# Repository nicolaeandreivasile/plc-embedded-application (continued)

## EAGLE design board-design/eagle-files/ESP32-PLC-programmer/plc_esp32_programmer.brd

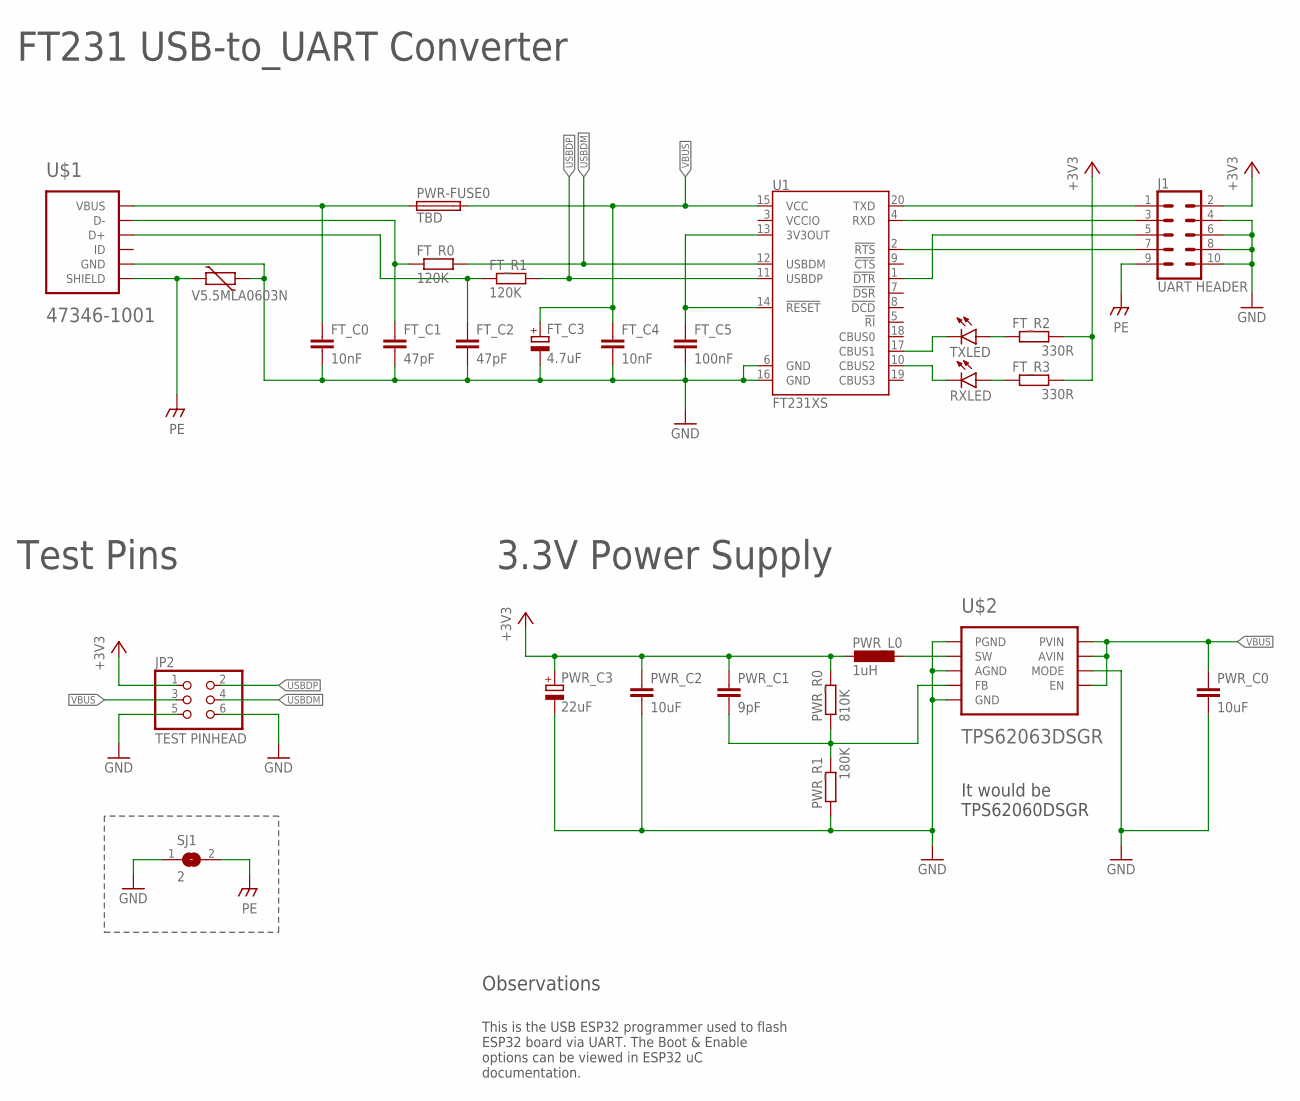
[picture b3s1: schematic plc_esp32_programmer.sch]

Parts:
FT_C0, FT_C4: 10nF; C0402
FT_C1, FT_C2: 47pF; C0402
FT_C3: 4.7uF; SMC_B
FT_C5: 100nF; C0402
FT_R0, FT_R1: 120K; R0402
FT_R2, FT_R3: 330R; R0402
J1: UART HEADER; 2X5-SHROUDED_SMD
JP2: TEST PINHEAD; 2X03
MCU_VAR1: V5.5MLA0603N; CT/CN0603
PWR-FUSE0: TBD; MF-SMDF050
PWR_C0, PWR_C2: 10uF; C0603
PWR_C1: 9pF; C0402
PWR_C3: 22uF; SMC_B
PWR_L0: 1uH; L1210
PWR_R0: 810K; R0402
PWR_R1: 180K; R0402
RXLED: LG_T679-E1F1-1; PLCC2
SJ1: 2; SJ
TXLED: LG_T679-E1F1-1; PLCC2
U1: FT231XS; SSOP20_L
U$1: 47346-1001
U$2: TPS62063DSGR; WSON-8

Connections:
+3V3: FT_R2.2, FT_R3.2, J1.2, JP2.1, PWR_C1.1, PWR_C2.1, PWR_C3.+, PWR_L0.2, PWR_R0.2
GND: FT_C0.2, FT_C1.2, FT_C2.2, FT_C3.-, FT_C4.2, FT_C5.2, J1.4, J1.6, J1.8, J1.10, JP2.5, JP2.6, MCU_VAR1.1, PWR_C0.2, PWR_C2.2, PWR_C3.-, PWR_R1.1, SJ1.1, U1.6 (GND), U1.16 (GND), U$1.5 (GND), U$2.1 (PGND), U$2.3 (AGND), U$2.6 (MODE), U$2.9 (GND), U$2.10 (GND), U$2.11 (GND)
unnamed: J1.1, U1.20 (TXD)
unnamed: J1.3, U1.4 (RXD)
unnamed: J1.7, U1.2 (!RTS)
unnamed: J1.5, U1.1 (!DTR)
unnamed: FT_C5.1, U1.13 (3V3OUT), U1.14 (!RESET)
unnamed: FT_C2.1, FT_R1.1, U$1.3 (D+)
unnamed: FT_C1.1, FT_R0.1, U$1.2 (D-)
unnamed: FT_C0.1, PWR-FUSE0.1, U$1.1 (VBUS)
unnamed: FT_R3.1, RXLED.A
unnamed: RXLED.C, U1.10 (CBUS2)
unnamed: PWR_L0.1, U$2.2 (SW)
unnamed: PWR_C1.2, PWR_R0.1, PWR_R1.2, U$2.4 (FB)
unnamed: FT_R2.1, TXLED.A
unnamed: TXLED.C, U1.17 (CBUS1)
PE: J1.9, MCU_VAR1.2, SJ1.2, U$1.6 (SHIELD), U$1.7 (SHIELD), U$1.8 (SHIELD), U$1.9 (SHIELD), U$1.10 (SHIELD), U$1.11 (SHIELD)
USBDM: FT_R0.2, JP2.4, U1.12 (USBDM)
USBDP: FT_R1.2, JP2.2, U1.11 (USBDP)
VBUS: FT_C3.+, FT_C4.1, JP2.3, PWR-FUSE0.2, PWR_C0.1, U1.15 (VCC), U$2.5 (EN), U$2.7 (AVIN), U$2.8 (PVIN)

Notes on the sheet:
It would be TPS62060DSGR
FT231 USB-to_UART Converter
3.3V Power Supply
Test Pins
Observations
This is the USB ESP32 programmer used to flash ESP32 board via UART. The Boot & Enable options can be viewed in ESP32 uC documentation.

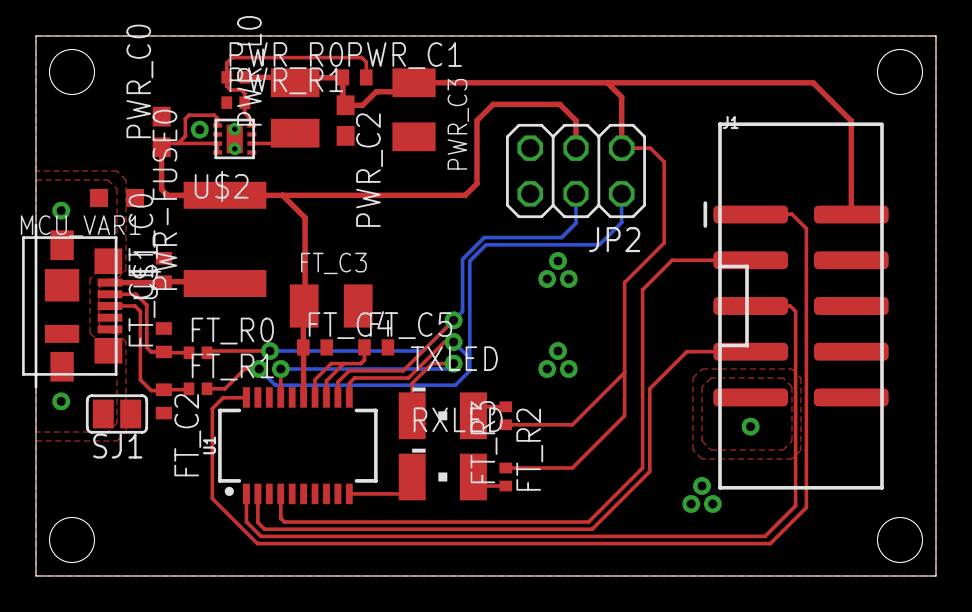
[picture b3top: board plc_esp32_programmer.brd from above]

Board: 2 copper layers, 50.0 x 30.0 mm, 27 parts (0 on the bottom side), 20 nets.

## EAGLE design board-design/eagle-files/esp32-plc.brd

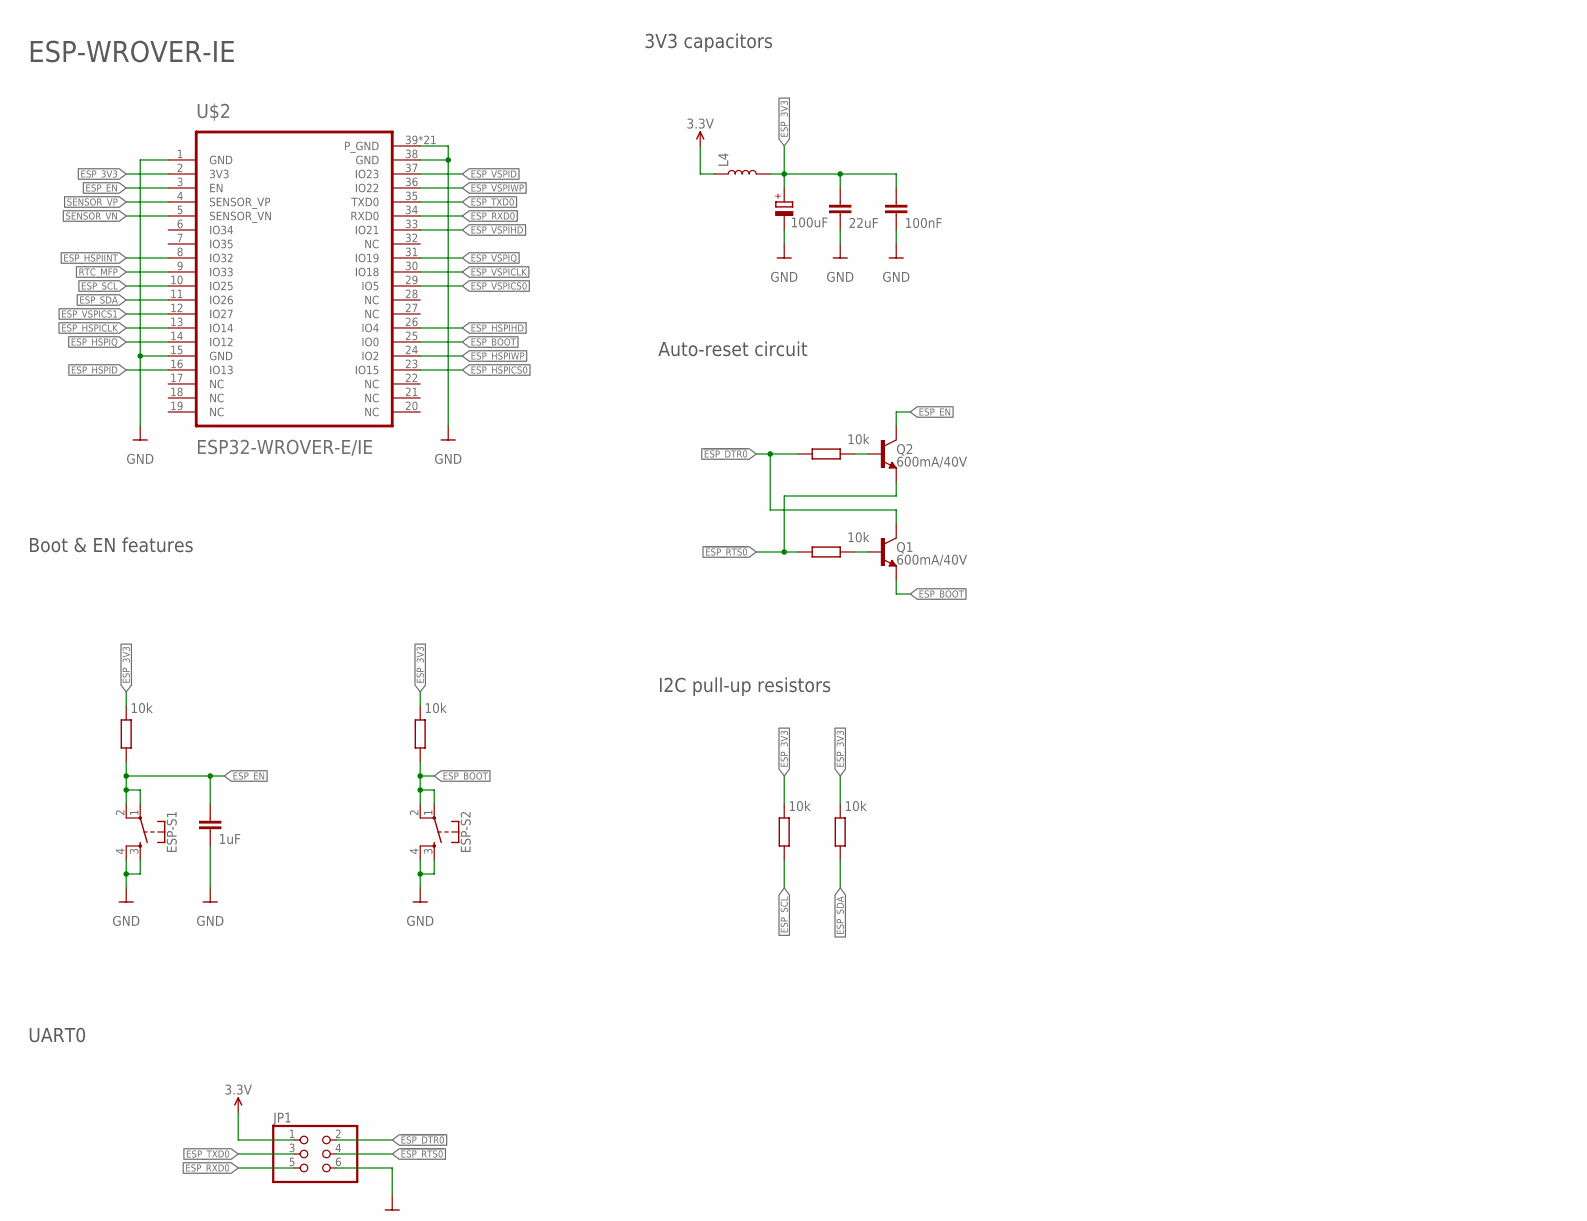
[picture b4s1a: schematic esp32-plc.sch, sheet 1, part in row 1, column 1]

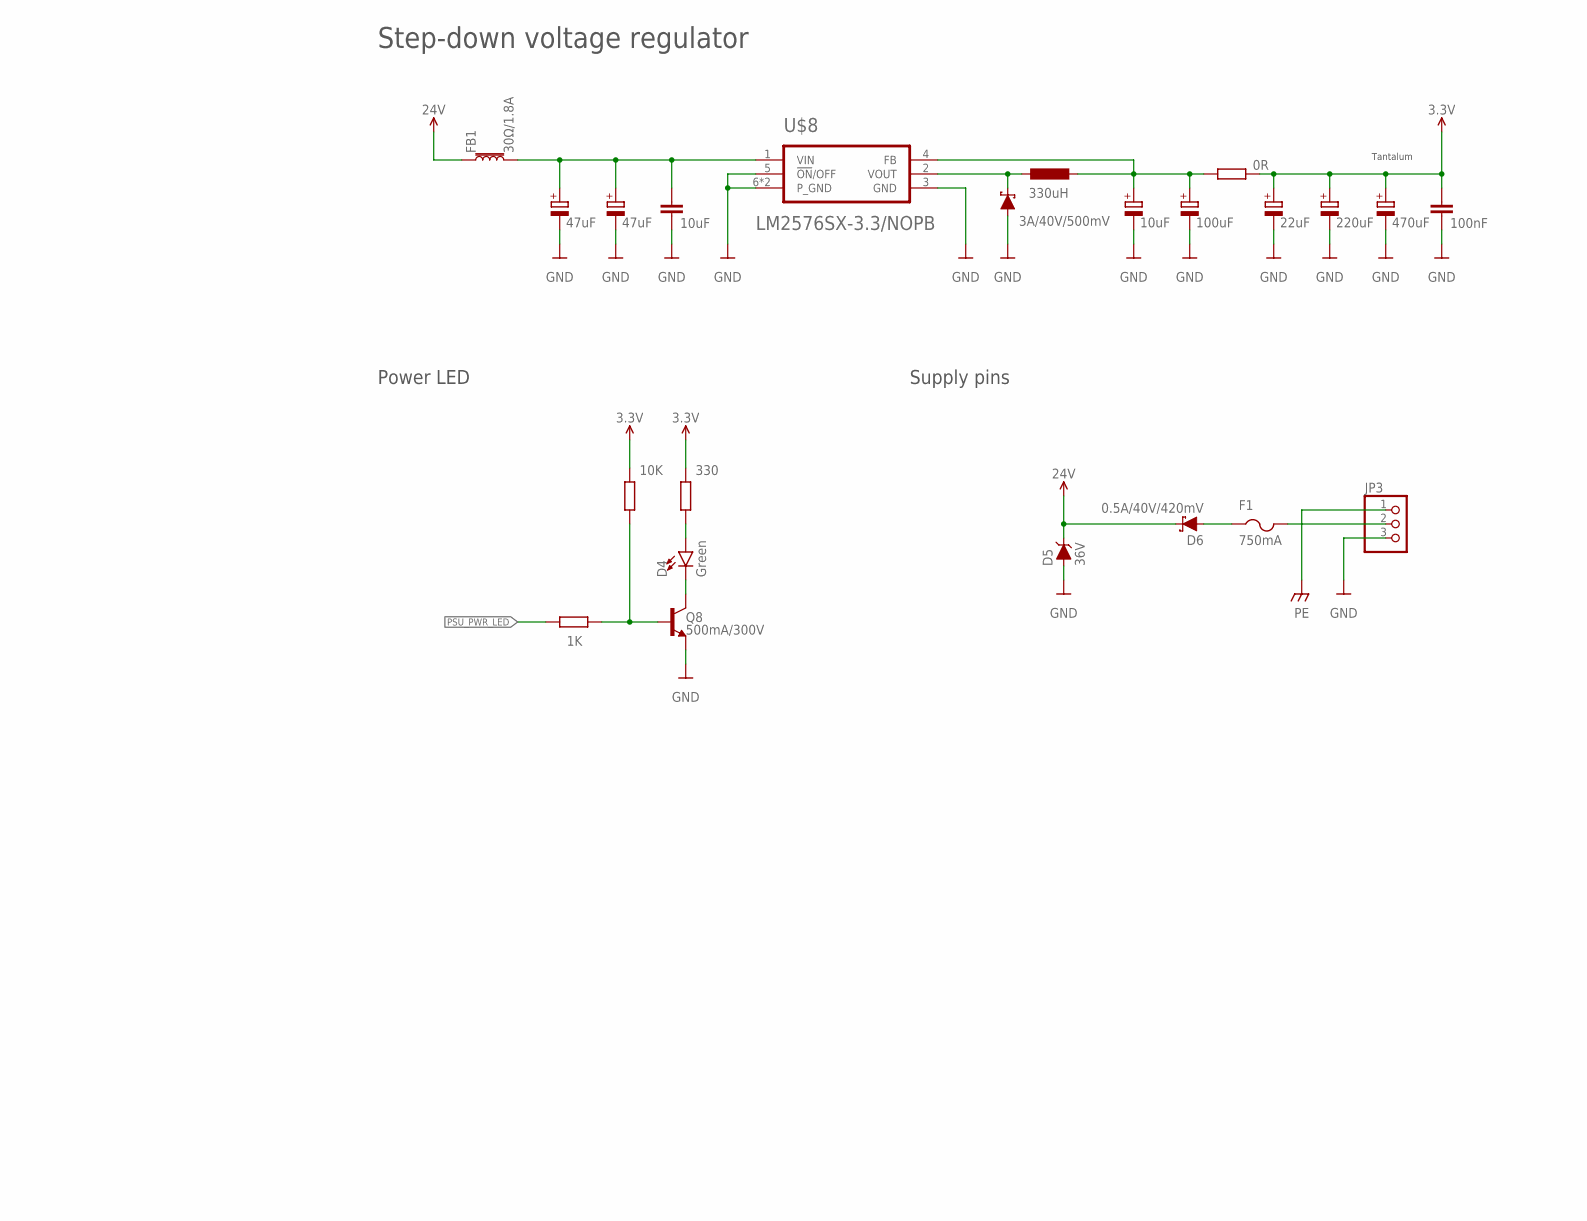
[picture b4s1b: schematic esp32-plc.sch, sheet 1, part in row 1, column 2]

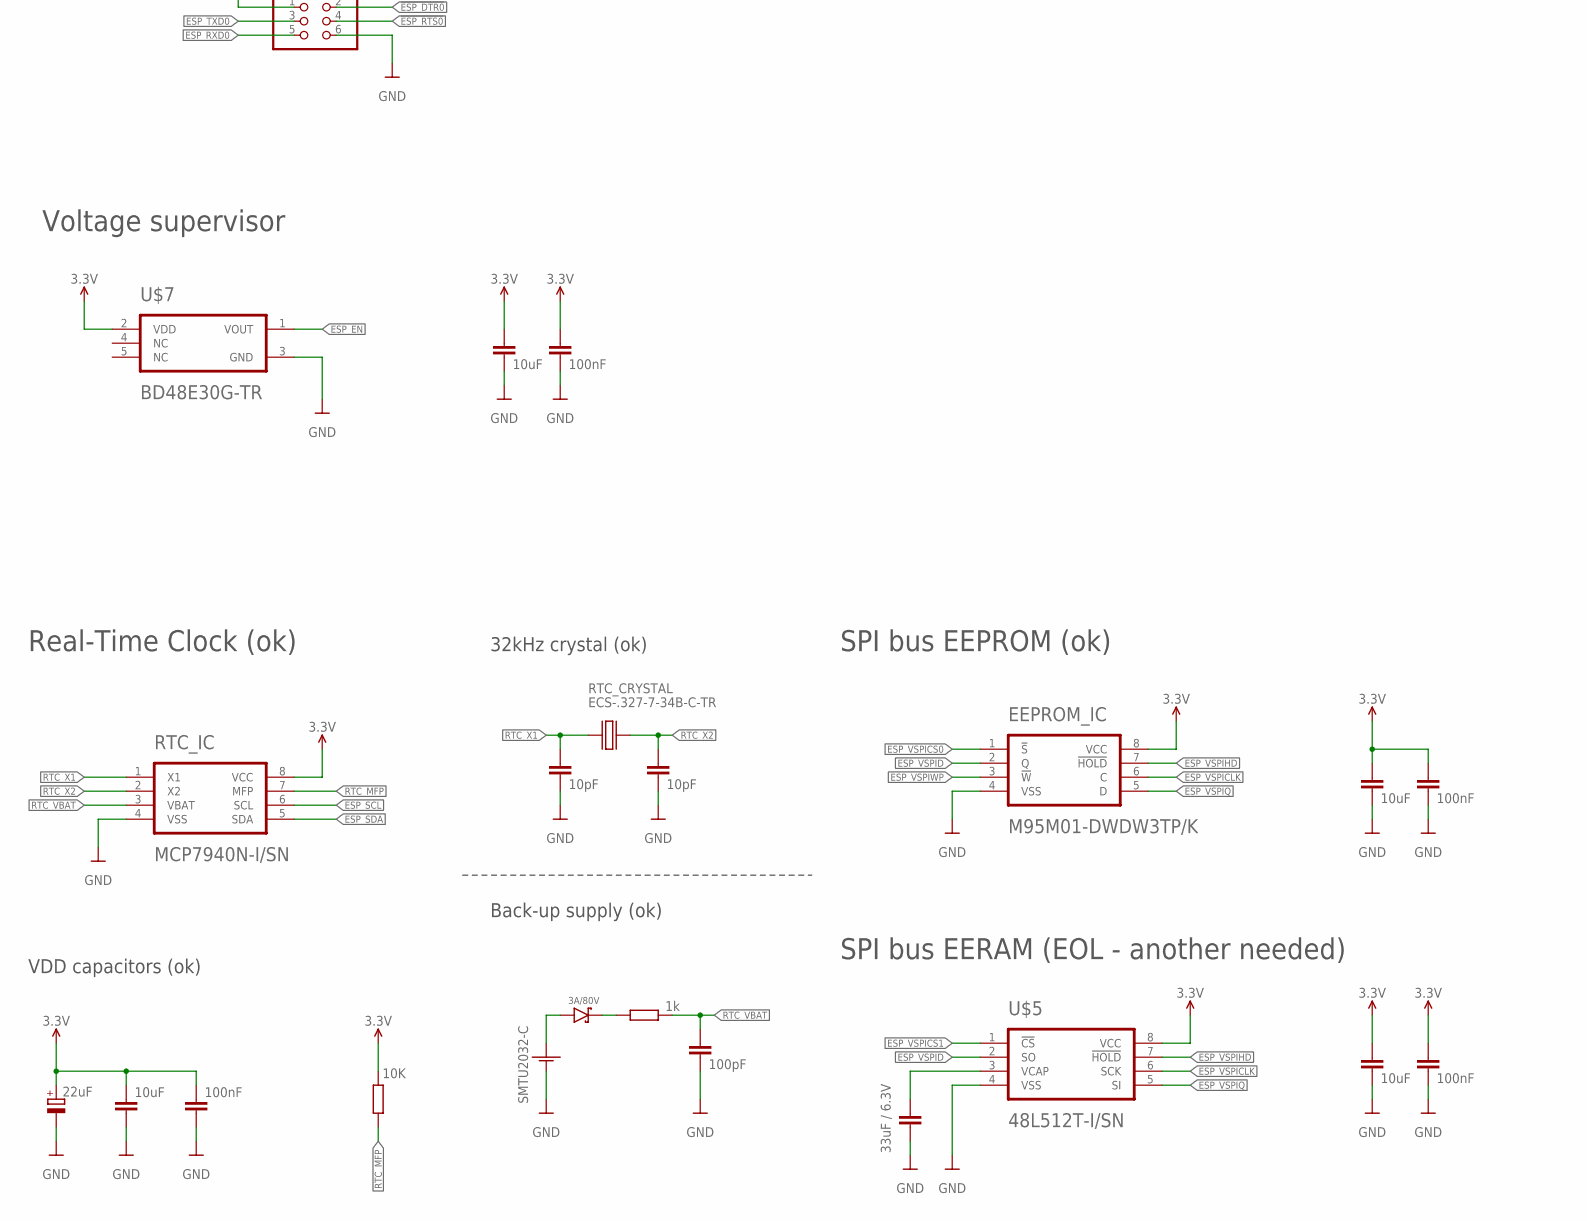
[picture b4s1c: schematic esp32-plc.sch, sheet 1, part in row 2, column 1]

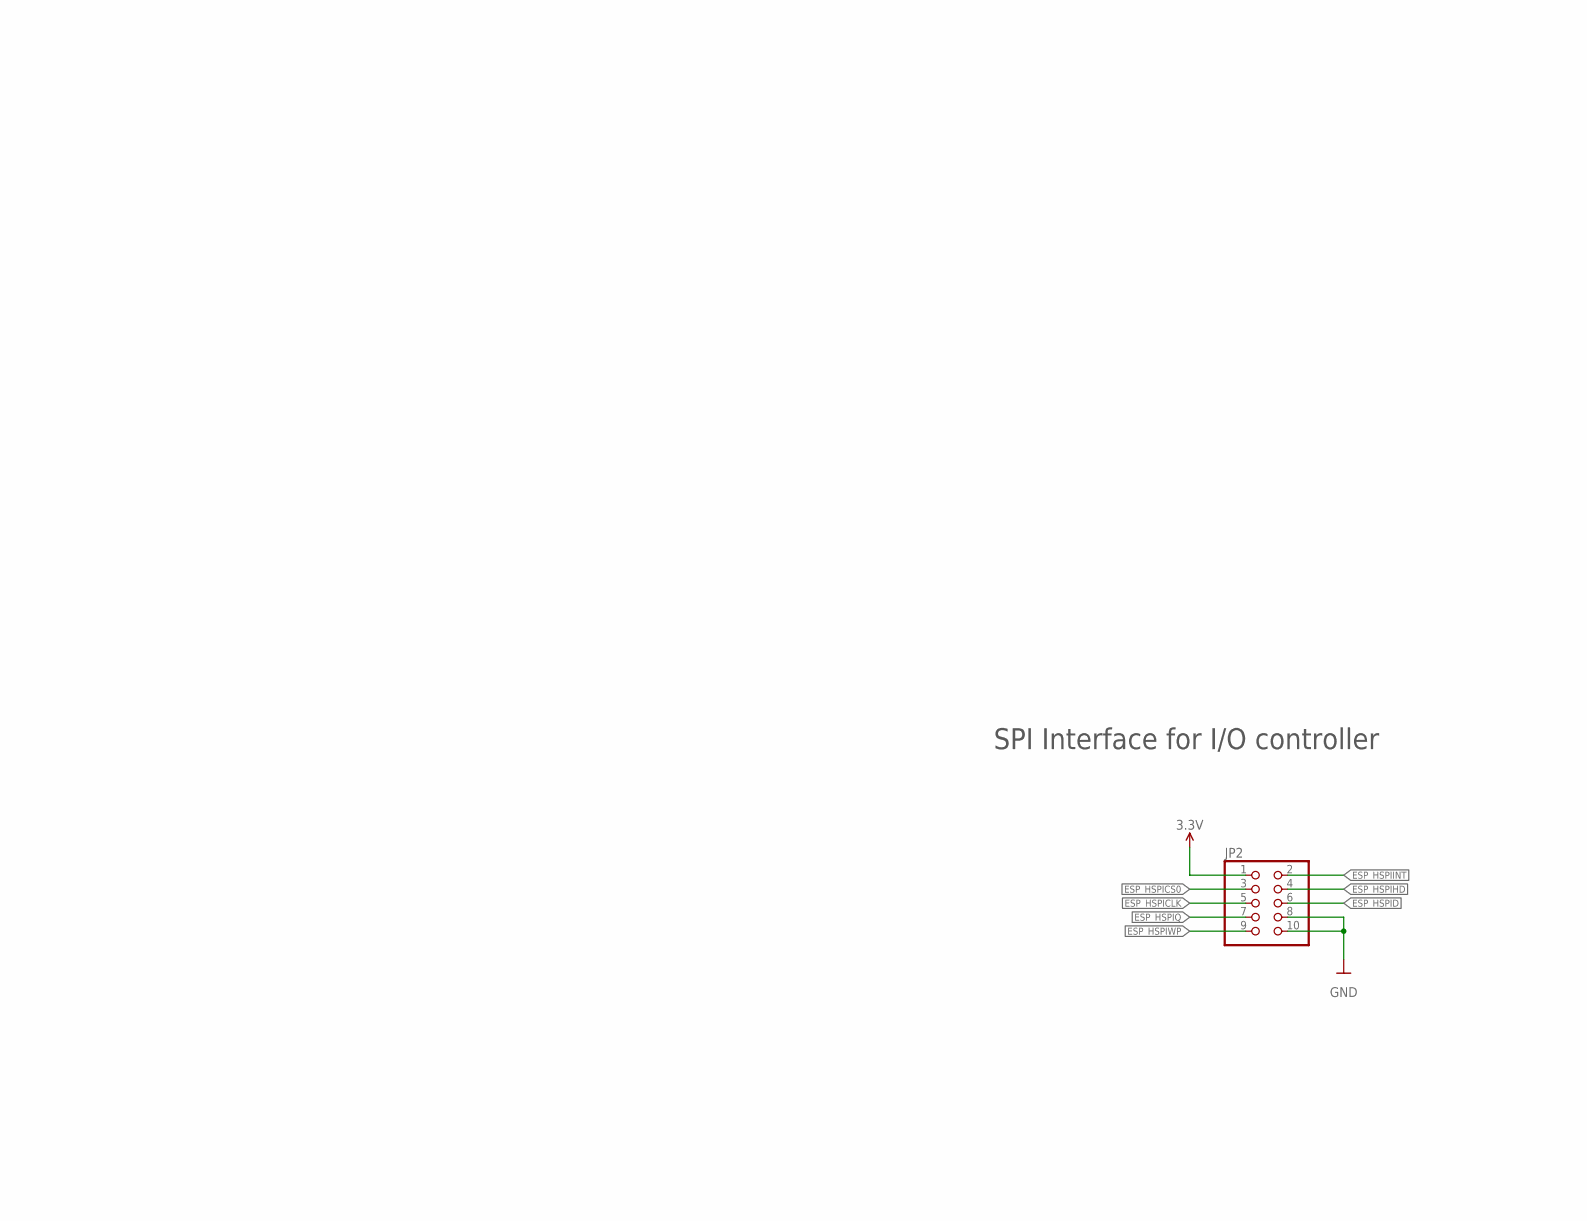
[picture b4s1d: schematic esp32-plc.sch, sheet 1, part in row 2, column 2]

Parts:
D3: 3A/40V/500mV; SMA-DIODE
D4: Green; LED-0603
D5: 36V; SOD-323
D6: 0.5A/40V/420mV; SOD-323
EEPROM-C0: 10uF; C0402
EEPROM-C1: 100nF; C0402
EEPROM_IC: M95M01-DWDW3TP/K; TSSOP-8
EERAM-C1: 100nF; C0402
EERAM-C2: 33uF / 6.3V; C0402
EERAM-C3: 10uF; C0402
ESP-C1: 22uF; C0402
ESP-C2: 100nF; C0402
ESP-C3: 1uF; C0402
ESP-R1, ESP-R2, ESP-R3, ESP-R4, ESP-R5, ESP-R6: 10k; R0402
ESP-S1, ESP-S2: MOMENTARY-SWITCH-SPST-2-SMD-4.6X2.8MM; TACTILE_SWITCH_SMD_4.6X2.8MM
ETH-C9: 22uF; C/6032-28R
F1: 750mA; R1206
FB1: 30Ω/1.8A; 0603
JP1: PINHD-2X3; 2X03
JP2: PINHD-2X5; 2X05
JP3: PINHD-1X3; 1X03
L1: 330uH; L1812
L4: INDUCTOR; XFL4020
LTE-VBAT-C11: 100uF; C/6032-28R
PSU-IN-C1, PSU-IN-C2: 47uF; C/6032-28R
PSU-IN-C3: 10uF; C0402
PSU-OUT-C1: 10uF; C/6032-28R
PSU-OUT-C2: 100uF; C/6032-28R
PSU-OUT-C3: 22uF; C/6032-28R
PSU-OUT-C4: 220uF; C/6032-28R
PSU-OUT-C5: 470uF; C/6032-28R
PSU-OUT-C6: 100nF; C0402
PSU-OUT-R1: 0R; R0402
PSU-OUT-R2: 330; R0402
PSU-OUT-R3: 10K; R0402
PSU-OUT-R4: 1K; R0402
Q1, Q2: 600mA/40V; SOT23-3
Q8: 500mA/300V; SOT23-3
RTC-C0: 10uF; C0402
RTC-C1: 100nF; C0402
RTC-C2, RTC-C3: 10pF; C0402
RTC-C4: 100pF; C0402
RTC-D0: 3A/80V; DO-220AA
RTC-R0: 1k; R0402
RTC-R2: 10K; R0402
RTC_BAT: SMTU2032-C; 32X20MM
RTC_CRYSTAL: ECS-.327-7-34B-C-TR; 3.2X1.5MM
RTC_IC: MCP7940N-I/SN; SOIC-8
U$2: ESP32-WROVER-E/IE
U$5: 48L512T-I/SN; SOIC-8
U$7: BD48E30G-TR; SSOP5
U$8: LM2576SX-3.3/NOPB; TO-263-5
VS-C1: 100nF; C0402
VS-C2: 10uF; C0402

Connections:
3.3V: EEPROM-C0.1, EEPROM-C1.1, EEPROM_IC.8 (VCC), EERAM-C1.1, EERAM-C3.1, ETH-C9.+, JP1.1, JP2.1, L4.P$1 (1), PSU-OUT-C3.+, PSU-OUT-C4.+, PSU-OUT-C5.+, PSU-OUT-C6.1, PSU-OUT-R1.1, PSU-OUT-R2.1, PSU-OUT-R3.1, RTC-C0.1, RTC-C1.1, RTC-R2.2, RTC_IC.8 (VCC), U$5.8 (VCC), U$7.2 (VDD), VS-C1.1, VS-C2.1; also elsewhere on the board
24V: D5.C, D6.C, FB1.1
!ESP_DTR0: ESP-R1.1, JP1.2, Q1.3 (C)
!ESP_RTS0: ESP-R2.1, JP1.4, Q2.2 (E)
EERAM_VCAP: EERAM-C2.1, U$5.3 (VCAP)
ESP_3V3: ESP-C1.1, ESP-C2.1, ESP-R3.2, ESP-R4.2, ESP-R5.2, ESP-R6.2, L4.P$2 (2), LTE-VBAT-C11.+, U$2.2 (3V3)
ESP_BOOT: ESP-R4.1, ESP-S2.1, ESP-S2.2, Q1.2 (E), U$2.25 (IO0)
ESP_EN: ESP-C3.1, ESP-R3.1, ESP-S1.1, ESP-S1.2, Q2.3 (C), U$2.3 (EN), U$7.1 (VOUT)
ESP_HSPICLK: JP2.5, U$2.13 (IO14)
ESP_HSPICS0: JP2.3, U$2.23 (IO15)
ESP_HSPID: JP2.6, U$2.16 (IO13)
ESP_HSPIHD: JP2.4, U$2.26 (IO4)
ESP_HSPIINT: JP2.2, U$2.8 (IO32)
ESP_HSPIQ: JP2.7, U$2.14 (IO12)
ESP_HSPIWP: JP2.9, U$2.24 (IO2)
ESP_RXD0: JP1.5, U$2.34 (RXD0)
ESP_SCL: ESP-R5.1, RTC_IC.6 (SCL), U$2.10 (IO25)
ESP_SDA: ESP-R6.1, RTC_IC.5 (SDA), U$2.11 (IO26)
ESP_TXD0: JP1.3, U$2.35 (TXD0)
ESP_VSPICLK: EEPROM_IC.6 (C), U$2.30 (IO18), U$5.6 (SCK)
ESP_VSPICS0: EEPROM_IC.1 (!S), U$2.29 (IO5)
ESP_VSPICS1: U$2.12 (IO27), U$5.1 (!CS)
ESP_VSPID: EEPROM_IC.2 (Q), U$2.37 (IO23), U$5.2 (SO)
ESP_VSPIHD: EEPROM_IC.7 (!HOLD), U$2.33 (IO21), U$5.7 (!HOLD)
ESP_VSPIQ: EEPROM_IC.5 (D), U$2.31 (IO19), U$5.5 (SI)
ESP_VSPIWP: EEPROM_IC.3 (!W), U$2.36 (IO22)
GND: D3.A, D5.A, EEPROM-C0.2, EEPROM-C1.2, EEPROM_IC.4 (VSS), EERAM-C1.2, EERAM-C2.2, EERAM-C3.2, ESP-C1.2, ESP-C2.2, ESP-C3.2, ESP-S1.3, ESP-S1.4, ESP-S2.3, ESP-S2.4, ETH-C9.-, JP1.6, JP2.8, JP2.10, JP3.3, LTE-VBAT-C11.-, PSU-IN-C1.-, PSU-IN-C2.-, PSU-IN-C3.2, PSU-OUT-C1.-, PSU-OUT-C2.-, PSU-OUT-C3.-, PSU-OUT-C4.-, PSU-OUT-C5.-, PSU-OUT-C6.2, Q8.2 (E), RTC-C0.2, RTC-C1.2, RTC-C2.2, RTC-C3.2, RTC-C4.2, RTC_BAT.2, RTC_IC.4 (VSS), U$2.1 (GND), U$2.15 (GND), U$2.38 (GND), U$2.39 (P_GND), U$2.40 (P_GND), U$2.41 (P_GND), U$2.42 (P_GND), U$2.43 (P_GND), U$2.44 (P_GND), U$2.45 (P_GND), U$2.46 (P_GND), U$2.47 (P_GND), U$2.48 (P_GND), U$2.49 (P_GND), U$2.50 (P_GND), U$2.51 (P_GND), U$2.52 (P_GND), U$2.53 (P_GND), U$2.54 (P_GND), U$2.55 (P_GND), U$2.56 (P_GND), U$2.57 (P_GND), U$2.58 (P_GND), U$2.59 (P_GND), U$5.4 (VSS), U$7.3 (GND), U$8.3 (GND), U$8.5 (!ON!/OFF), U$8.6 (P_GND), U$8.7 (P_GND), VS-C1.2, VS-C2.2; also elsewhere on the board
unnamed: D4.C, Q8.3 (C)
unnamed: D4.A, PSU-OUT-R2.2
unnamed: RTC-D0.2, RTC-R0.2
unnamed: RTC-D0.1, RTC_BAT.1
unnamed: PSU-OUT-R3.2, PSU-OUT-R4.1, Q8.1 (B)
unnamed: F1.2, JP3.2
unnamed: FB1.2, PSU-IN-C1.+, PSU-IN-C2.+, PSU-IN-C3.1, U$8.1 (VIN)
unnamed: D6.A, F1.1
unnamed: L1.2, PSU-OUT-C1.+, PSU-OUT-C2.+, PSU-OUT-R1.2, U$8.4 (FB)
unnamed: D3.C, L1.1, U$8.2 (VOUT)
unnamed: ESP-R2.2, Q1.1 (B)
unnamed: ESP-R1.2, Q2.1 (B)
P$1: JP3.1
PSU_PWR_LED: PSU-OUT-R4.2
RTC_MFP: RTC-R2.1, RTC_IC.7 (MFP), U$2.9 (IO33)
RTC_VBAT: RTC-C4.1, RTC-R0.1, RTC_IC.3 (VBAT)
RTC_X1: RTC-C2.1, RTC_CRYSTAL.1, RTC_IC.1 (X1)
RTC_X2: RTC-C3.1, RTC_CRYSTAL.2, RTC_IC.2 (X2)
SENSOR_VN: U$2.5 (SENSOR_VN)
SENSOR_VP: U$2.4 (SENSOR_VP)

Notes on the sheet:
Auto-reset circuit
ESP-WROVER-IE
3V3 capacitors
Boot & EN features
I2C pull-up resistors
Step-down voltage regulator
Tantalum
Supply pins
Power LED
SPI bus EEPROM (ok)
Real-Time Clock (ok)
Back-up supply (ok)
32kHz crystal (ok)
SPI bus EERAM (EOL - another needed)
SPI Interface for I/O controller
Voltage supervisor
UART0
VDD capacitors (ok)
